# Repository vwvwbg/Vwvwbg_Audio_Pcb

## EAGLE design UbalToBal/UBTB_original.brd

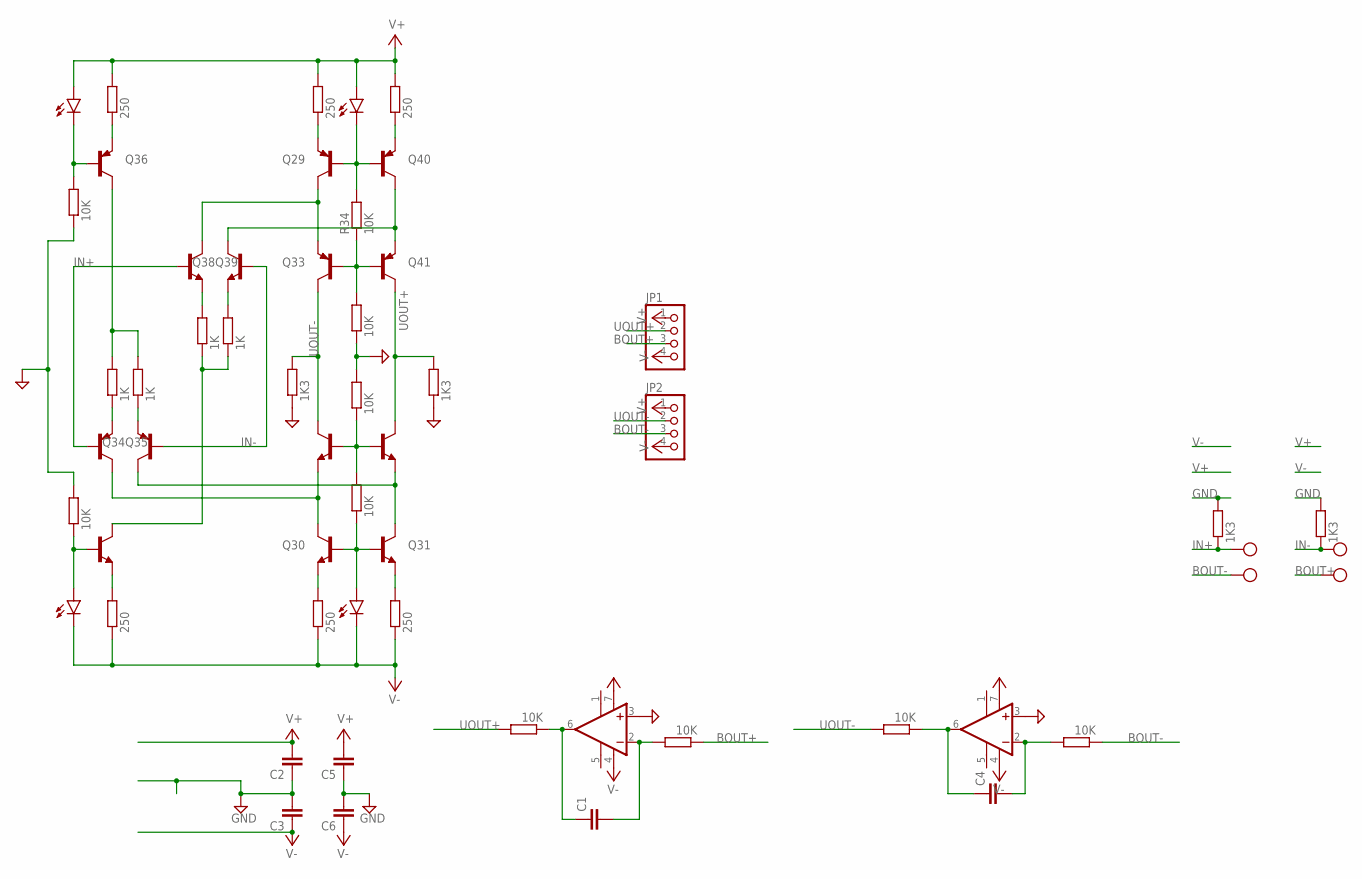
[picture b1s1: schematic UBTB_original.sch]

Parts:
C1, C4: C-EUC1206; C1206
C2, C3, C5, C6: C-EUC0805; C0805
IC1, IC2: OPA627U; SO08
JP1, JP2: PINHD-1X4; 1X04
LED1, LED2, LED3, LED4: LEDCHIPLED_1206; CHIPLED_1206
Q26, Q30, Q31, Q32, Q37, Q38, Q39: BC847CSMD; SOT23
Q29, Q33, Q34, Q35, Q36, Q40, Q41: BC857CSMD; SOT23-BEC
R1, R2, R37, R38: 1K3; MINI_MELF-0204W
R16, R17, R29, R32, R33, R34, R45, R46, R48, R51: 10K; MINI_MELF-0204W
R22, R23, R35, R36, R43, R44: 250; MINI_MELF-0204W
R39, R40, R41, R42: 1K; MINI_MELF-0204W
X3, X4: CON-PHOENIX-508_MKDSN1,5/2-5,08

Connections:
BOUT+: JP1.3, R17.1, X4.2
BOUT-: JP2.3, R48.1, X3.2
GND: C2.1, C3.2, C5.1, C6.2, IC1.3 (+IN), IC2.3 (+IN), R1.2, R2.2, R32.2, R33.1, R37.1, R38.1, R45.1, R46.2
IN+: Q35.B, Q39.1 (B), R1.1, X3.1
IN-: Q34.B, Q38.1 (B), R2.1, X4.1
unnamed: C4.1, IC2.6 (OUT), R51.1
unnamed: C4.2, IC2.2 (-IN), R48.2
unnamed: C1.2, IC1.2 (-IN), R17.2
unnamed: C1.1, IC1.6 (OUT), R16.1
unnamed: Q30.2 (E), R22.2
unnamed: Q31.2 (E), R23.2
unnamed: Q31.3 (C), Q32.2 (E), Q34.C
unnamed: Q30.3 (C), Q35.C, Q37.2 (E)
unnamed: LED1.A, Q30.1 (B), Q31.1 (B), R29.1
unnamed: Q32.1 (B), Q37.1 (B), R29.2, R32.1
unnamed: Q33.B, Q41.B, R33.2, R34.1
unnamed: Q29.C, Q33.E, Q39.3 (C)
unnamed: LED2.C, Q29.B, Q40.B, R34.2
unnamed: Q38.3 (C), Q40.C, Q41.E
unnamed: Q29.E, R35.1
unnamed: Q40.E, R36.1
unnamed: LED3.C, Q36.B, R45.2
unnamed: Q36.E, R43.1
unnamed: Q36.C, R41.2, R42.2
unnamed: Q34.E, R42.1
unnamed: Q35.E, R41.1
unnamed: Q39.2 (E), R39.2
unnamed: Q38.2 (E), R40.2
unnamed: Q26.3 (C), R39.1, R40.1
unnamed: Q26.2 (E), R44.2
unnamed: LED4.A, Q26.1 (B), R46.1
UOUT+: JP1.2, Q32.3 (C), Q41.C, R16.2, R38.2
UOUT-: JP2.2, Q33.C, Q37.3 (C), R37.2, R51.2
V+: C2.2, C5.2, IC1.7 (V+), IC2.7 (V+), JP1.1, JP2.1, LED2.A, LED3.A, R35.2, R36.2, R43.2
V-: C3.1, C6.1, IC1.4 (V-), IC2.4 (V-), JP1.4, JP2.4, LED1.C, LED4.C, R22.1, R23.1, R44.1

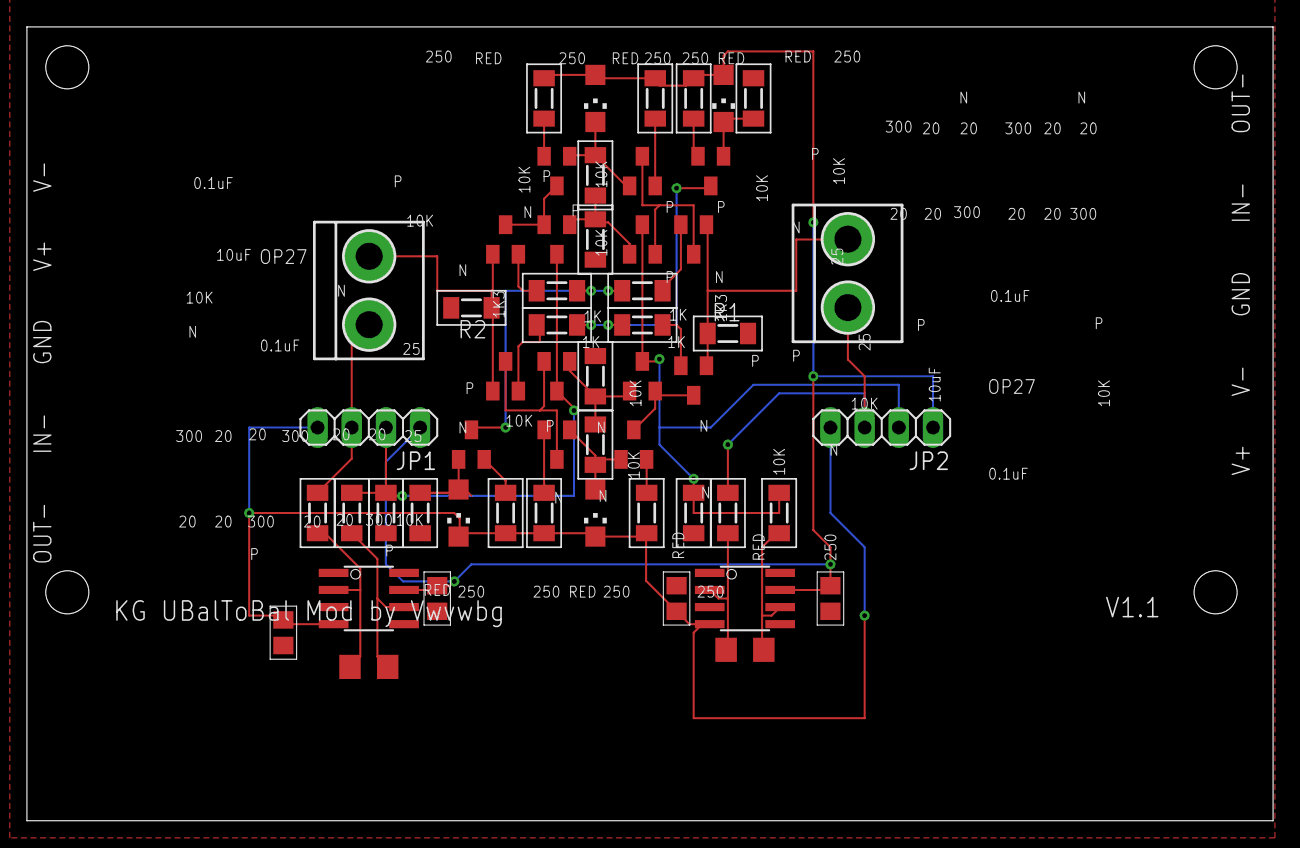
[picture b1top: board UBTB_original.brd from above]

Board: 2 copper layers, 92.6 x 59.0 mm, 54 parts (0 on the bottom side), 35 nets.

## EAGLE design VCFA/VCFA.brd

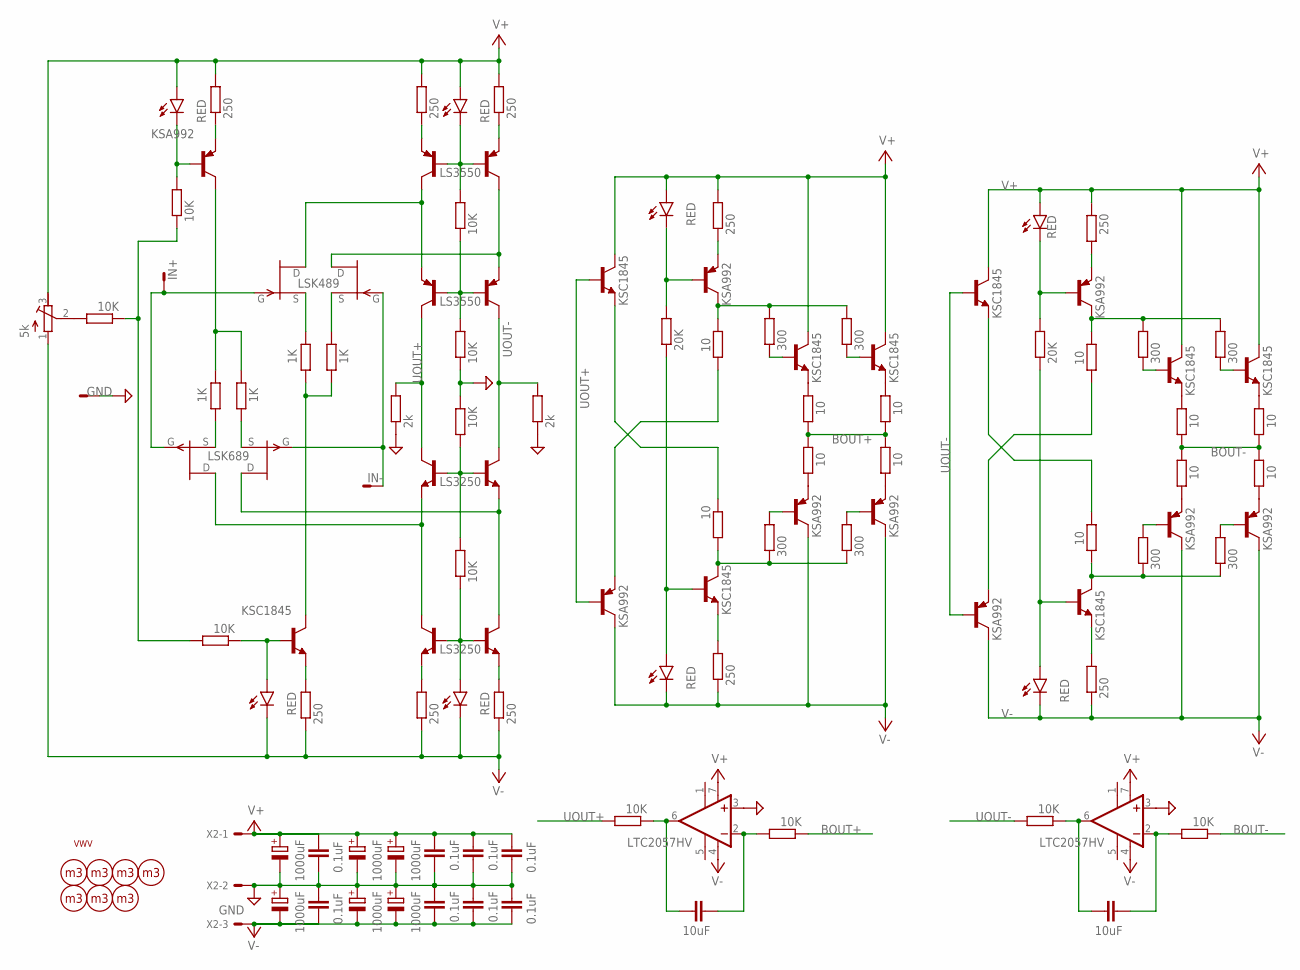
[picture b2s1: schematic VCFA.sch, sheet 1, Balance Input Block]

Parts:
C1, C2, C5, C6, C7, C8: 1000uF; E7,5-16
C3, C4, C14, C15: 0.1uF; C0805
C9, C10, C11, C12: 0.1uF; C050-045X075
C13, C16: 10uF; C1206
H1, H2, H3, H4, H5, H6, H7: HOLE; M3_HOLE
IC1, IC2: LTC2057HV; SO08
LED1, LED2, LED3, LED4, LED5, LED6, LED7, LED8: RED; LED_SML1206
Q1: LSK689; SOT-23-6
Q2, Q10, Q11, Q14, Q16, Q18, Q19, Q22, Q24: KSA992; TRANSISTOR_TO92-ECB_P
Q3, Q9, Q12, Q13, Q15, Q17, Q20, Q21, Q23: KSC1845; TRANSISTOR_TO92-ECB_N
Q4: LSK489; SOT-23-6
Q5, Q8: LS3550; SOT-23-6
Q6, Q7: LS3250; SOT-23-6
R1: 5k; RTRIM3296W
R2, R3, R4, R14, R15, R16, R17, R21, R29, R36, R44: 10K; MINI_MELF-0204W
R5, R7, R12, R13, R18, R19, R23, R26, R38, R41: 250; MINI_MELF-0204W
R6, R8, R9, R10: 1K; MINI_MELF-0204W
R11, R20: 2k; MINI_MELF-0204W
R22, R37: 20K; MINI_MELF-0204W
R24, R25, R30, R31, R34, R35, R39, R40, R45, R46, R49, R50: 10; MINI_MELF-0204W
R27, R28, R32, R33, R42, R43, R47, R48: 300; MINI_MELF-0204W
S1: VWV
X1, X2: KK-156-3

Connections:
BOUT+: R29.1, R30.1, R31.2, R34.1, R35.2; also elsewhere on the board
BOUT-: R44.1, R45.1, R46.2, R49.1, R50.2; also elsewhere on the board
GND: C1.-, C2.+, C3.1, C4.2, C5.-, C6.+, C7.-, C8.+, C9.2, C10.1, C11.2, C12.1, C14.1, C15.2, IC1.3 (+IN), IC2.3 (+IN), R11.1, R15.1, R16.2, R20.1, X1.2, X2.2; also elsewhere on the board
IN+: Q1.1 (G), Q4.1 (G), X1.1
IN-: Q1.4 (G), Q4.4 (G), X1.3
unnamed: Q8.2 (E), R12.1
unnamed: Q10.E, R24.2
unnamed: Q12.E, R26.2
unnamed: Q11.E, R23.1
unnamed: LED5.C, Q11.B, R22.2
unnamed: LED6.A, Q12.B, R22.1
unnamed: Q11.C, R24.1, R27.2, R32.2
unnamed: Q12.C, R25.2, R28.1, R33.1
unnamed: Q9.E, R25.1
unnamed: Q13.B, R27.1
unnamed: Q13.E, R30.2
unnamed: Q16.B, R33.2
unnamed: Q15.B, R32.1
unnamed: Q14.B, R28.2
unnamed: Q14.E, R31.1
unnamed: C13.2, IC1.2 (-IN), R29.2
unnamed: Q15.E, R34.2
unnamed: Q16.E, R35.1
unnamed: C13.1, IC1.6 (OUT), R21.1
unnamed: Q8.5 (E), R18.1
unnamed: R2.1, R3.1, R4.2
unnamed: Q20.E, R41.2
unnamed: Q19.E, R38.1
unnamed: LED7.C, Q19.B, R37.2
unnamed: LED8.A, Q20.B, R37.1
unnamed: Q19.C, R39.1, R42.2, R47.2
unnamed: Q20.C, R40.2, R43.1, R48.1
unnamed: Q18.E, R39.2
unnamed: Q17.E, R40.1
unnamed: Q21.B, R42.1
unnamed: Q22.B, R43.2
unnamed: Q23.B, R47.1
unnamed: Q24.B, R48.2
unnamed: Q21.E, R45.2
unnamed: Q22.E, R46.1
unnamed: Q23.E, R49.2
unnamed: Q24.E, R50.1
unnamed: C16.2, IC2.2 (-IN), R44.2
unnamed: C16.1, IC2.6 (OUT), R36.1
unnamed: R1.2 (S), R2.2
unnamed: Q7.5 (E), R13.2
unnamed: Q7.2 (E), R19.2
unnamed: Q1.5 (D), Q6.2 (E), Q7.4 (C)
unnamed: Q1.2 (D), Q6.5 (E), Q7.6 (C)
unnamed: LED4.A, Q7.1 (B), Q7.3 (B), R17.1
unnamed: Q6.1 (B), Q6.3 (B), R16.1, R17.2
unnamed: LED2.A, Q3.B, R4.1
unnamed: Q5.1 (B), Q5.3 (B), R14.1, R15.2
unnamed: Q4.2 (D), Q5.5 (E), Q8.4 (C)
unnamed: LED3.C, Q8.1 (B), Q8.3 (B), R14.2
unnamed: Q4.5 (D), Q5.2 (E), Q8.6 (C)
unnamed: LED1.C, Q2.B, R3.2
unnamed: Q2.E, R5.1
unnamed: Q2.C, R6.2, R8.2
unnamed: Q1.6 (S), R8.1
unnamed: Q1.3 (S), R6.1
unnamed: Q4.3 (S), R9.2
unnamed: Q4.6 (S), R10.2
unnamed: Q3.C, R9.1, R10.1
unnamed: Q3.E, R7.2
UOUT+: Q5.6 (C), Q6.6 (C), Q9.B, Q10.B, R11.2, R21.2
UOUT-: Q5.4 (C), Q6.4 (C), Q17.B, Q18.B, R20.2, R36.2
V+: C1.+, C3.2, C5.+, C7.+, C9.1, C11.1, C14.2, IC1.7 (V+), IC2.7 (V+), LED1.A, LED3.A, LED5.A, LED7.A, Q9.C, Q13.C, Q15.C, Q17.C, Q21.C, Q23.C, R1.3 (E), R5.2, R12.2, R18.2, R23.2, R38.2, X2.1; also elsewhere on the board
V-: C2.-, C4.1, C6.-, C8.-, C10.2, C12.2, C15.1, IC1.4 (V-), IC2.4 (V-), LED2.C, LED4.C, LED6.C, LED8.C, Q10.C, Q14.C, Q16.C, Q18.C, Q22.C, Q24.C, R1.1 (A), R7.1, R13.1, R19.1, R26.1, R41.1, X2.3; also elsewhere on the board

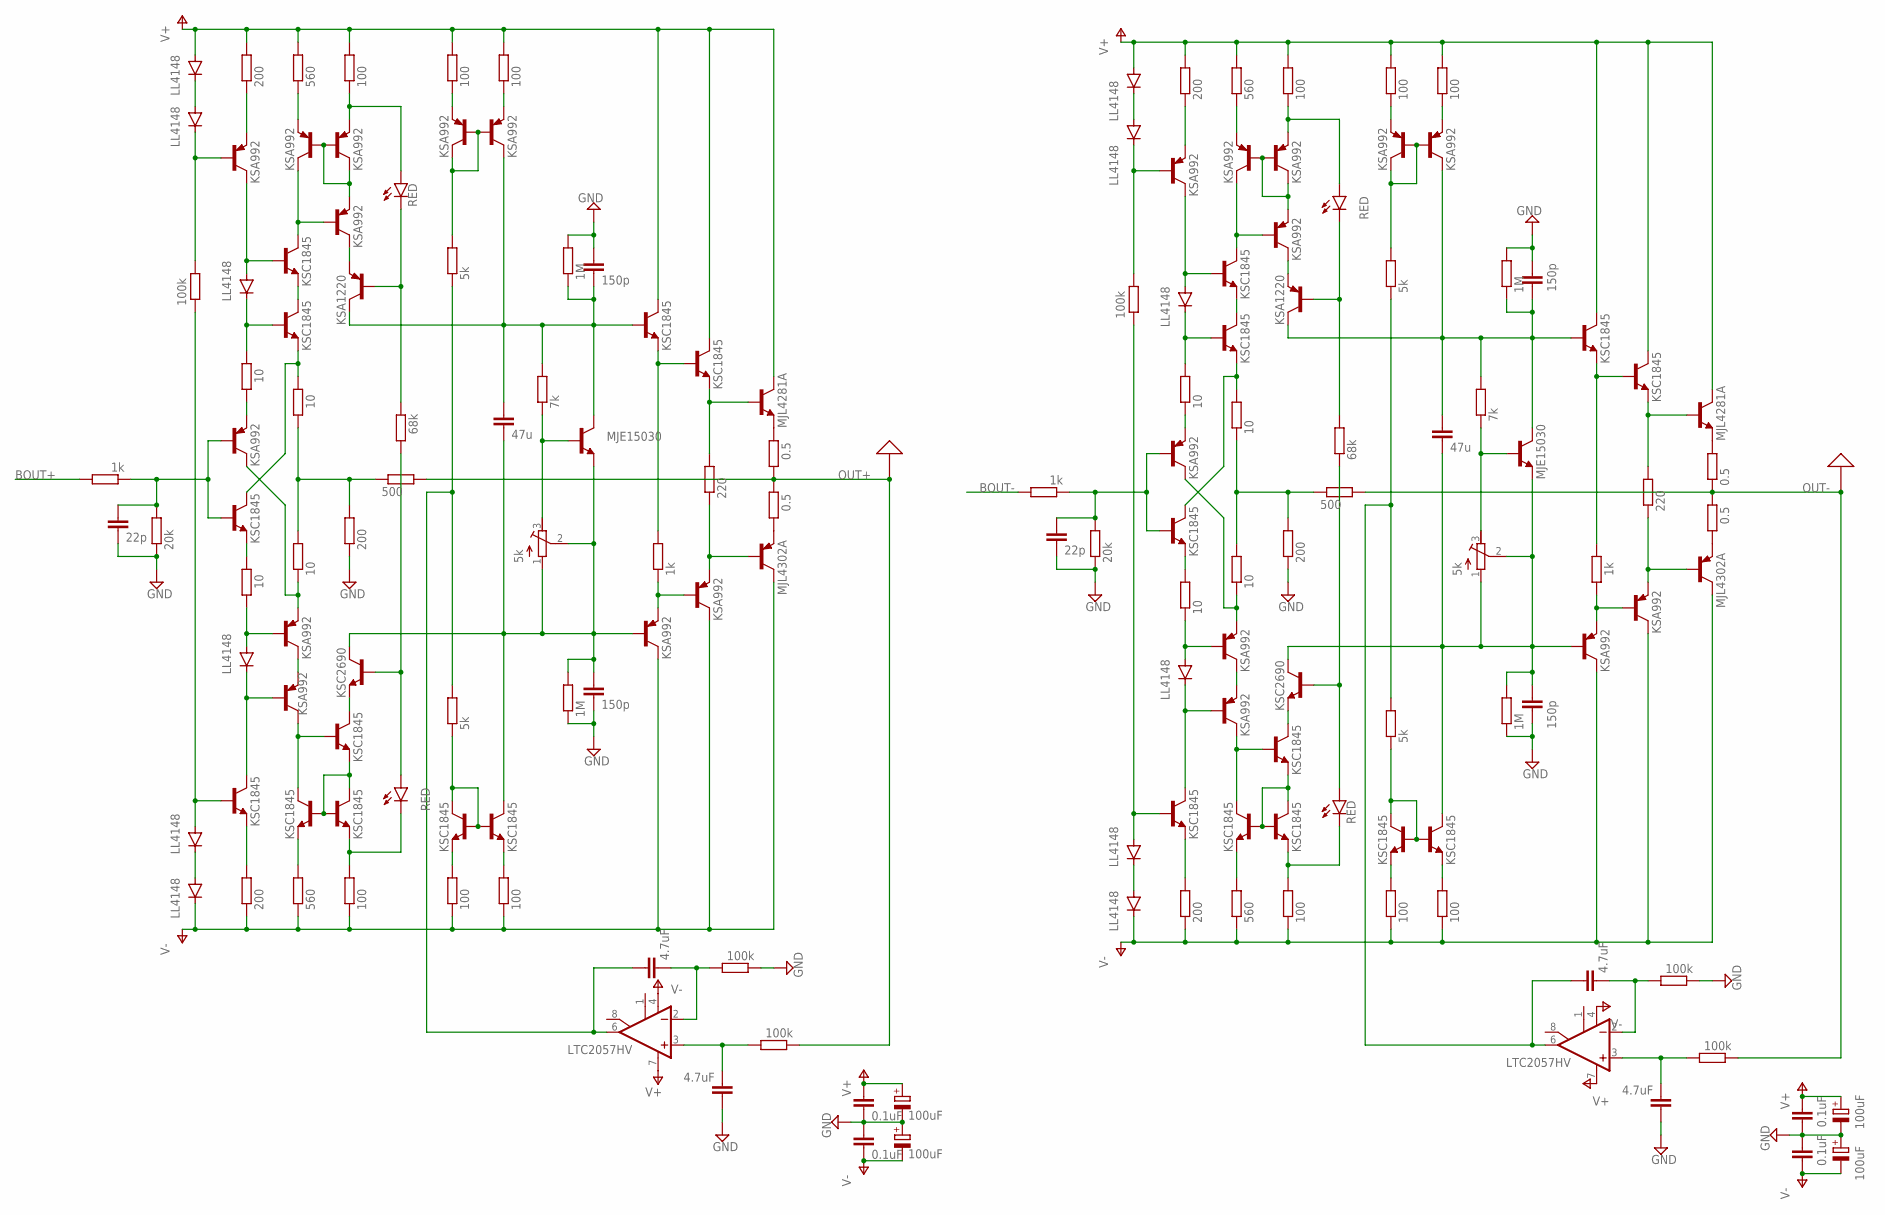
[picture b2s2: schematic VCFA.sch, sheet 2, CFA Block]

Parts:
C17, C27: 22p; C0805
C18, C28: 47u; C1210
C19, C20, C29, C30: 150p; C0805
C21, C22, C31, C32: 4.7uF; C1210
C23, C24, C33, C34: 0.1uF; C0603K
C25, C26, C35, C36: 100uF; E3,5-8
D1, D2, D3, D4, D5, D6, D7, D8, D9, D10, D11, D12: LL4148; SOD80C
IC3, IC4: LTC2057HV; SOIC8
LED9, LED10, LED11, LED12: RED; LED_SML1206
PAD1, PAD2: PAD; PAD-16
Q25, Q26, Q31, Q32, Q33, Q35, Q36, Q41, Q43, Q47, Q49, Q52, Q53, Q58, Q59, Q60, Q62, Q63, Q68, Q70, Q74, Q76: KSA992; TRANSISTOR_TO92-ECB_P
Q27, Q28, Q29, Q30, Q34, Q37, Q38, Q42, Q44, Q46, Q48, Q54, Q55, Q56, Q57, Q61, Q64, Q65, Q69, Q71, Q73, Q75: KSC1845; TRANSISTOR_TO92-ECB_N
Q39, Q66: KSA1220; TRANSISTOR_TO126_P
Q40, Q67: KSC2690; TRANSISTOR_TO126_N
Q45, Q72: MJE15030; TRANSISTOR_TO220_BCE_N
Q50, Q77: MJL4281A; TRANSISTOR_TO247_BCE_N
Q51, Q78: MJL4302A; TRANSISTOR_TO247_BCE_P
R51, R77, R83, R109: 1k; MINI_MELF-0204W
R52, R84: 20k; MINI_MELF-0204W
R53, R79, R82, R85, R111, R114: 100k; MINI_MELF-0204W
R54, R57, R63, R86, R89, R95: 200; MINI_MELF-0204W
R55, R56, R59, R60, R87, R88, R91, R92: 10; MINI_MELF-0204W
R58, R61, R90, R93: 560; MINI_MELF-0204W
R62, R64, R67, R70, R71, R72, R94, R96, R99, R102, R103, R104: 100; MINI_MELF-0204W
R65, R97: 68k; MINI_MELF-0204W
R66, R98: 500; MINI_MELF-0204W
R68, R69, R100, R101: 5k; MINI_MELF-0204W
R73, R105: 7k; MINI_MELF-0204W
R74, R106: 5k; RTRIM3296W
R75, R76, R107, R108: 1M; MINI_MELF-0204W
R78, R110: 220; MINI_MELF-0204W
R80, R81, R112, R113: 0.5; R2512

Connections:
BOUT+: R51.2; also elsewhere on the board
BOUT-: R83.2; also elsewhere on the board
GND: C17.2, C19.1, C20.2, C22.1, C23.2, C24.1, C25.-, C26.+, C27.2, C29.1, C30.2, C32.1, C33.2, C34.1, C35.-, C36.+, R52.1, R63.1, R75.2, R76.1, R79.1, R84.1, R95.1, R107.2, R108.1, R111.1; also elsewhere on the board
unnamed: Q25.E, R54.1
unnamed: D5.A, Q25.C, Q29.B
unnamed: D1.C, D2.A
unnamed: D2.C, Q25.B, R53.2
unnamed: D5.C, Q30.B, R55.2
unnamed: Q29.E, Q30.C
unnamed: Q27.C, Q30.E, R59.2
unnamed: R59.1, R60.2, R63.2, R66.1
unnamed: Q26.C, Q31.E, R60.1
unnamed: D6.A, Q31.B, R56.1
unnamed: D6.C, Q28.C, Q32.B
unnamed: Q28.E, R57.2
unnamed: D3.C, D4.A
unnamed: Q31.C, Q32.E
unnamed: Q26.E, R55.1
unnamed: Q27.E, R56.2
unnamed: C17.1, Q26.B, Q27.B, R51.1, R52.2
unnamed: Q29.C, Q33.C, Q36.B
unnamed: Q33.B, Q35.B, Q35.C, Q36.E
unnamed: Q33.E, R58.1
unnamed: LED9.A, Q35.E, R62.1
unnamed: Q36.C, Q39.E
unnamed: LED9.C, Q39.B, R65.2
unnamed: Q34.B, Q37.E, Q38.B, Q38.C
unnamed: LED10.C, Q38.E, R64.2
unnamed: Q34.E, R61.2
unnamed: Q32.C, Q34.C, Q37.B
unnamed: Q37.C, Q40.E
unnamed: LED10.A, Q40.B, R65.1
unnamed: C18.1, C19.2, Q39.C, Q43.C, Q45.C, Q46.B, R73.2, R75.1
unnamed: Q41.B, Q41.C, Q43.B, R68.2
unnamed: Q42.B, Q42.C, Q44.B, R69.1
unnamed: Q41.E, R67.1
unnamed: Q43.E, R71.1
unnamed: Q42.E, R70.2
unnamed: Q44.E, R72.2
unnamed: Q46.E, Q48.B, R77.2
unnamed: Q47.E, Q49.B, R77.1
unnamed: C18.2, C20.1, Q40.C, Q44.C, Q45.E, Q47.B, R74.1 (A), R74.2 (S), R76.2
unnamed: Q48.E, Q50.B, R78.2
unnamed: Q49.E, Q51.B, R78.1
unnamed: Q50.E, R80.2
unnamed: Q51.E, R81.1
unnamed: C21.2, IC3.2 (-IN), R79.2
unnamed: C22.2, IC3.3 (+IN), R82.2
unnamed: D3.A, Q28.B, R53.1
unnamed: Q45.B, R73.1, R74.3 (E)
unnamed: C21.1, IC3.6 (OUT), R68.1, R69.2
unnamed: Q52.E, R86.1
unnamed: D11.A, Q52.C, Q56.B
unnamed: D7.C, D8.A
unnamed: D8.C, Q52.B, R85.2
unnamed: D11.C, Q57.B, R87.2
unnamed: Q56.E, Q57.C
unnamed: Q54.C, Q57.E, R91.2
unnamed: R91.1, R92.2, R95.2, R98.1
unnamed: Q53.C, Q58.E, R92.1
unnamed: D12.A, Q58.B, R88.1
unnamed: D12.C, Q55.C, Q59.B
unnamed: Q55.E, R89.2
unnamed: D9.C, D10.A
unnamed: Q58.C, Q59.E
unnamed: Q53.E, R87.1
unnamed: Q54.E, R88.2
unnamed: C27.1, Q53.B, Q54.B, R83.1, R84.2
unnamed: Q56.C, Q60.C, Q63.B
unnamed: Q60.B, Q62.B, Q62.C, Q63.E
unnamed: Q60.E, R90.1
unnamed: LED11.A, Q62.E, R94.1
unnamed: Q63.C, Q66.E
unnamed: LED11.C, Q66.B, R97.2
unnamed: Q61.B, Q64.E, Q65.B, Q65.C
unnamed: LED12.C, Q65.E, R96.2
unnamed: Q61.E, R93.2
unnamed: Q59.C, Q61.C, Q64.B
unnamed: Q64.C, Q67.E
unnamed: LED12.A, Q67.B, R97.1
unnamed: C28.1, C29.2, Q66.C, Q70.C, Q72.C, Q73.B, R105.2, R107.1
unnamed: Q68.B, Q68.C, Q70.B, R100.2
unnamed: Q69.B, Q69.C, Q71.B, R101.1
unnamed: Q68.E, R99.1
unnamed: Q70.E, R103.1
unnamed: Q69.E, R102.2
unnamed: Q71.E, R104.2
unnamed: Q73.E, Q75.B, R109.2
unnamed: Q74.E, Q76.B, R109.1
unnamed: C28.2, C30.1, Q67.C, Q71.C, Q72.E, Q74.B, R106.1 (A), R106.2 (S), R108.2
unnamed: Q75.E, Q77.B, R110.2
unnamed: Q76.E, Q78.B, R110.1
unnamed: Q77.E, R112.2
unnamed: Q78.E, R113.1
unnamed: C31.2, IC4.2 (-IN), R111.2
unnamed: C32.2, IC4.3 (+IN), R114.2
unnamed: D9.A, Q55.B, R85.1
unnamed: Q72.B, R105.1, R106.3 (E)
unnamed: C31.1, IC4.6 (OUT), R100.1, R101.2
OUT+: PAD1.P$1, R66.2, R80.1, R81.2, R82.1
OUT-: PAD2.P$1, R98.2, R112.1, R113.2, R114.1
V+: C23.1, C25.+, C33.1, C35.+, D1.A, D7.A, IC3.7 (V+), IC4.7 (V+), Q46.C, Q48.C, Q50.C, Q73.C, Q75.C, Q77.C, R54.2, R58.2, R62.2, R67.2, R71.2, R86.2, R90.2, R94.2, R99.2, R103.2; also elsewhere on the board
V-: C24.2, C26.-, C34.2, C36.-, D4.C, D10.C, IC3.4 (V-), IC4.4 (V-), Q47.C, Q49.C, Q51.C, Q74.C, Q76.C, Q78.C, R57.1, R61.1, R64.1, R70.1, R72.1, R89.1, R93.1, R96.1, R102.1, R104.1; also elsewhere on the board

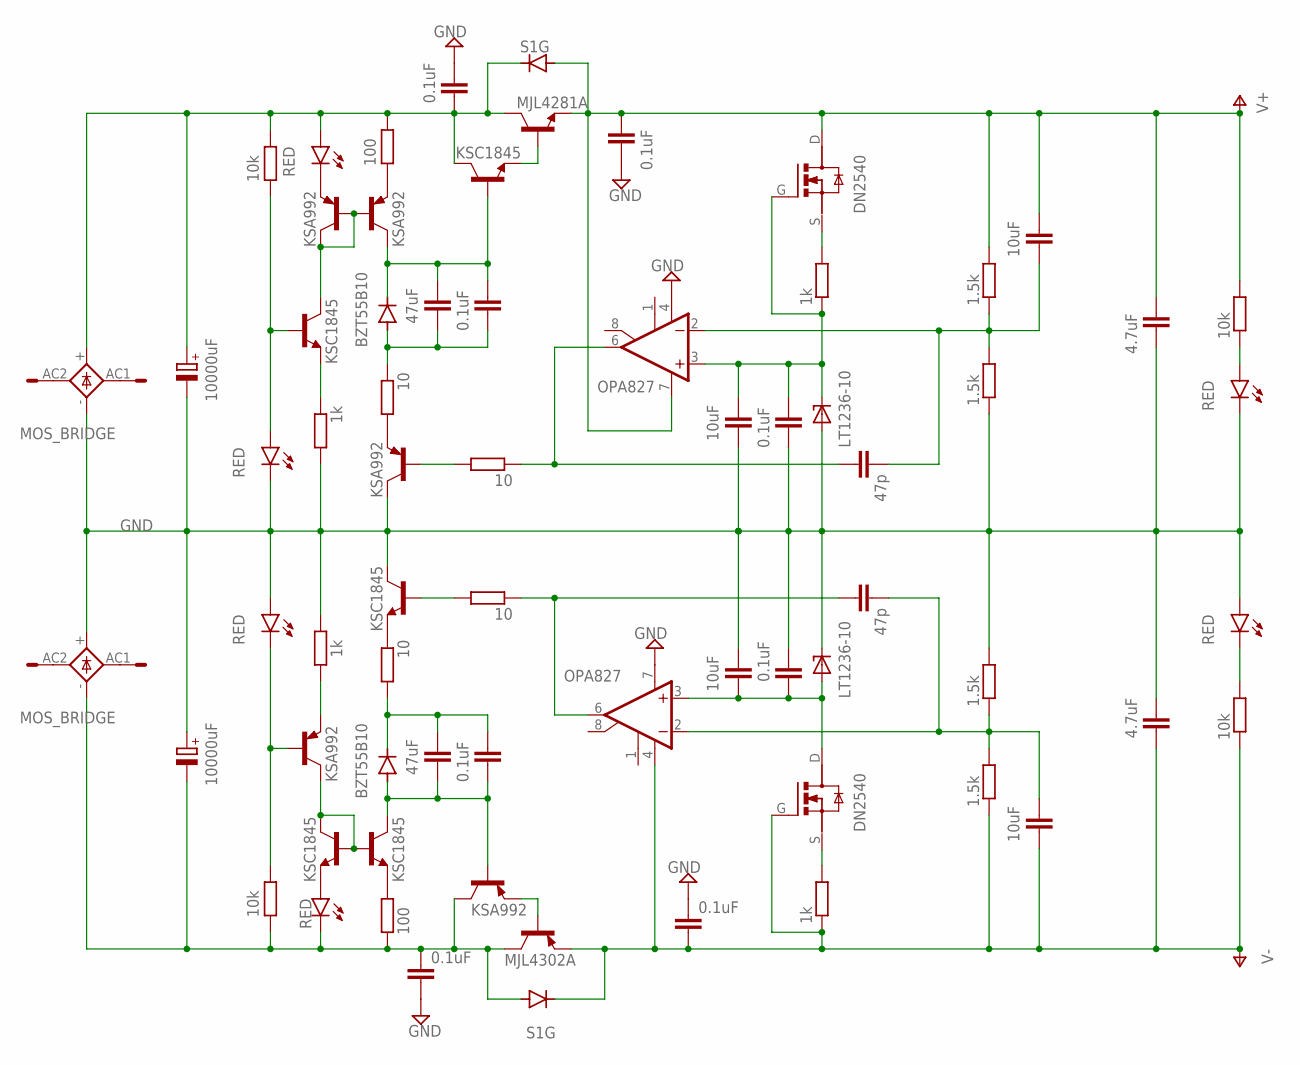
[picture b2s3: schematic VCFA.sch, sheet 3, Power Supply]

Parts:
B1, B2: MOS_BRIDGE; GBU4S
C37, C38: 10000uF; EB35D
C39, C42: 0.1uF; C050-075X075
C40, C41: 47uF; C1206
C43, C44, C45, C46, C49, C50: 0.1uF; C0805
C47, C48, C53, C54: 10uF; C1206
C51, C52: 47p; C0805
C55, C56: 4.7uF; C050-075X075
D13, D14: BZT55B10; SOD80C
D15, D16: S1G; DO214AA
D17, D18: LT1236-10; SO8
IC5, IC6: OPA827; SOIC8
LED13, LED14, LED15, LED16, LED17, LED18: RED; LED_SML1206
Q79, Q82, Q84, Q86, Q87: KSC1845; TRANSISTOR_TO92-ECB_N
Q80, Q81, Q83, Q85, Q88: KSA992; TRANSISTOR_TO92-ECB_P
Q89: MJL4281A; TRANSISTOR_TO247_BCE_N
Q90: MJL4302A; TRANSISTOR_TO247_BCE_P
Q91, Q92: DN2540; TRANSISTOR_TO92-SGD_N
R115, R116, R131, R132: 10k; MINI_MELF-0204W
R117, R118, R125, R126: 1k; MINI_MELF-0204W
R119, R122: 100; MINI_MELF-0204W
R120, R121, R123, R124: 10; MINI_MELF-0204W
R127, R128, R129, R130: 1.5k; MINI_MELF-0204W
X3, X4: KK-156-2

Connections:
GND: B1.-, B2.+, C37.-, C38.+, C39.1, C42.2, C45.1, C46.2, C47.2, C48.1, C49.2, C50.1, C55.1, C56.2, D17.4 (GND), D18.6 (OUT), IC5.7 (V+), IC6.4 (V-), LED13.C, LED14.A, LED17.C, LED18.A, Q85.C, Q86.C, R117.2, R118.1, R128.1, R129.2; also elsewhere on the board
unnamed: Q79.C, Q81.B, Q81.C, Q83.B
unnamed: LED15.C, Q81.E
unnamed: Q83.E, R119.2
unnamed: B1.+, C37.+, C42.1, D15.C, LED15.A, Q87.C, Q89.C, R115.1, R119.1
unnamed: C40.1, C43.1, D13.C, Q83.C, Q87.B
unnamed: C40.2, C43.2, D13.A, R120.1
unnamed: Q85.E, R120.2
unnamed: Q79.E, R117.1
unnamed: LED13.A, Q79.B, R115.2
unnamed: Q80.E, R118.2
unnamed: LED14.C, Q80.B, R116.1
unnamed: Q86.E, R121.1
unnamed: C41.1, C44.1, D14.C, R121.2
unnamed: C41.2, C44.2, D14.A, Q84.C, Q88.B
unnamed: Q80.C, Q82.B, Q82.C, Q84.B
unnamed: Q84.E, R122.1
unnamed: LED16.A, Q82.E
unnamed: Q88.E, Q90.B
unnamed: Q87.E, Q89.B
unnamed: C51.1, IC6.6 (OUT), R123.1
unnamed: C52.1, IC5.6 (OUT), R124.1
unnamed: Q86.B, R124.2
unnamed: Q85.B, R123.2
unnamed: C51.2, C53.2, IC6.2 (-IN), R127.1, R128.2
unnamed: C47.1, C49.1, D17.6 (OUT), IC6.3 (+IN), Q91.G, R125.1
unnamed: Q91.S, R125.2
unnamed: C48.2, C50.2, D18.4 (GND), IC5.3 (+IN), Q92.D
unnamed: Q92.S, R126.2
unnamed: C52.2, C54.1, IC5.2 (-IN), R129.1, R130.2
unnamed: LED18.C, R132.2
unnamed: LED17.A, R131.1
unnamed: B2.-, C38.-, C39.2, D16.A, LED16.C, Q88.C, Q90.C, R116.2, R122.2
unnamed: B1.AC2 (AC1), X3.1
unnamed: B1.AC1 (AC2), X3.2
unnamed: B2.AC2 (AC1), X4.2
unnamed: B2.AC1 (AC2), X4.1
V+: C45.2, C53.1, C55.2, D15.A, IC6.7 (V+), Q89.E, Q91.D, R127.2, R131.2; also elsewhere on the board
V-: C46.1, C54.2, C56.1, D16.C, IC5.4 (V-), Q90.E, Q92.G, R126.1, R130.1, R132.1; also elsewhere on the board

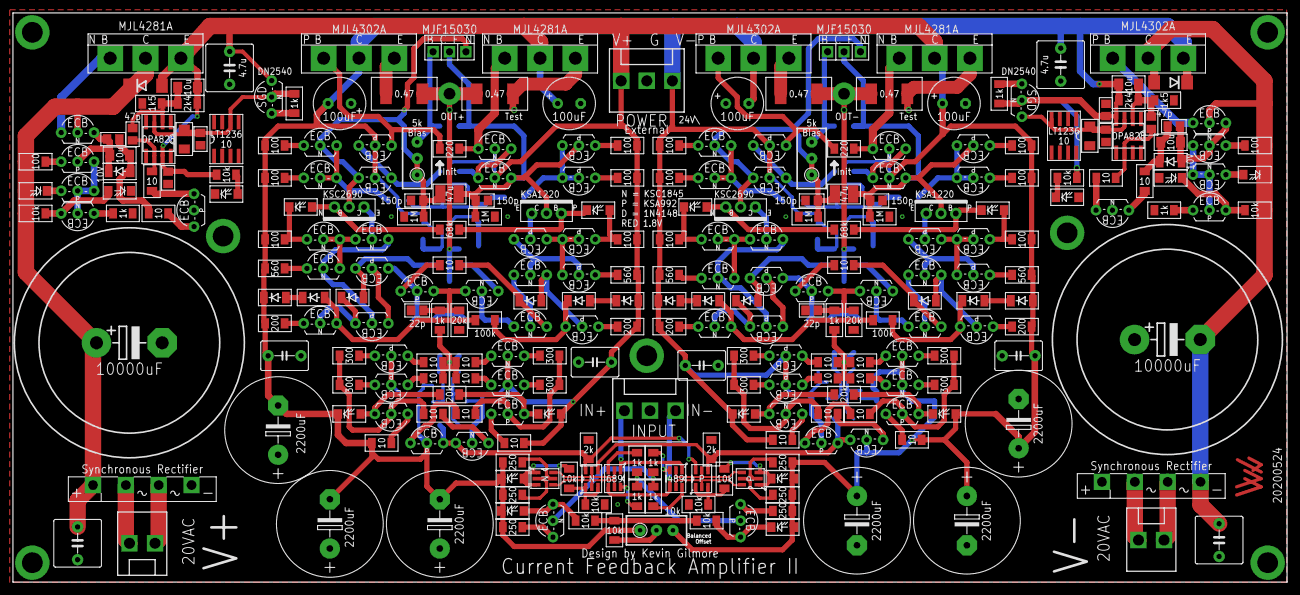
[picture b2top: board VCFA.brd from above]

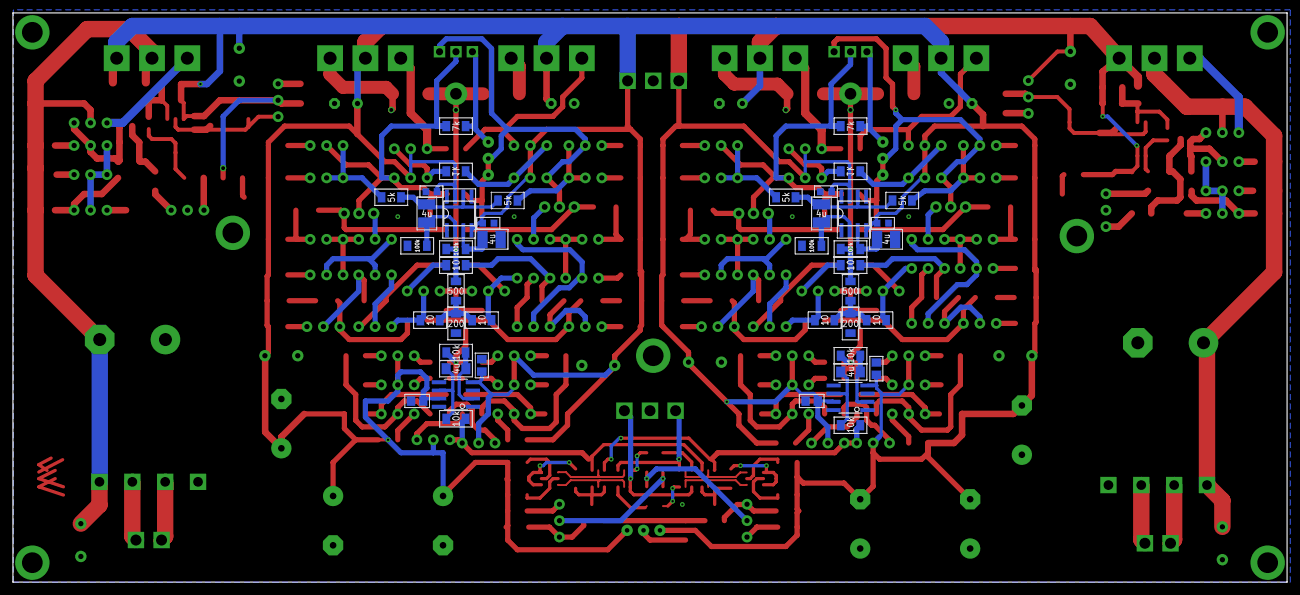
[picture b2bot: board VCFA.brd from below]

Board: 2 copper layers, 197.0 x 88.0 mm, 338 parts (45 on the bottom side), 203 nets.

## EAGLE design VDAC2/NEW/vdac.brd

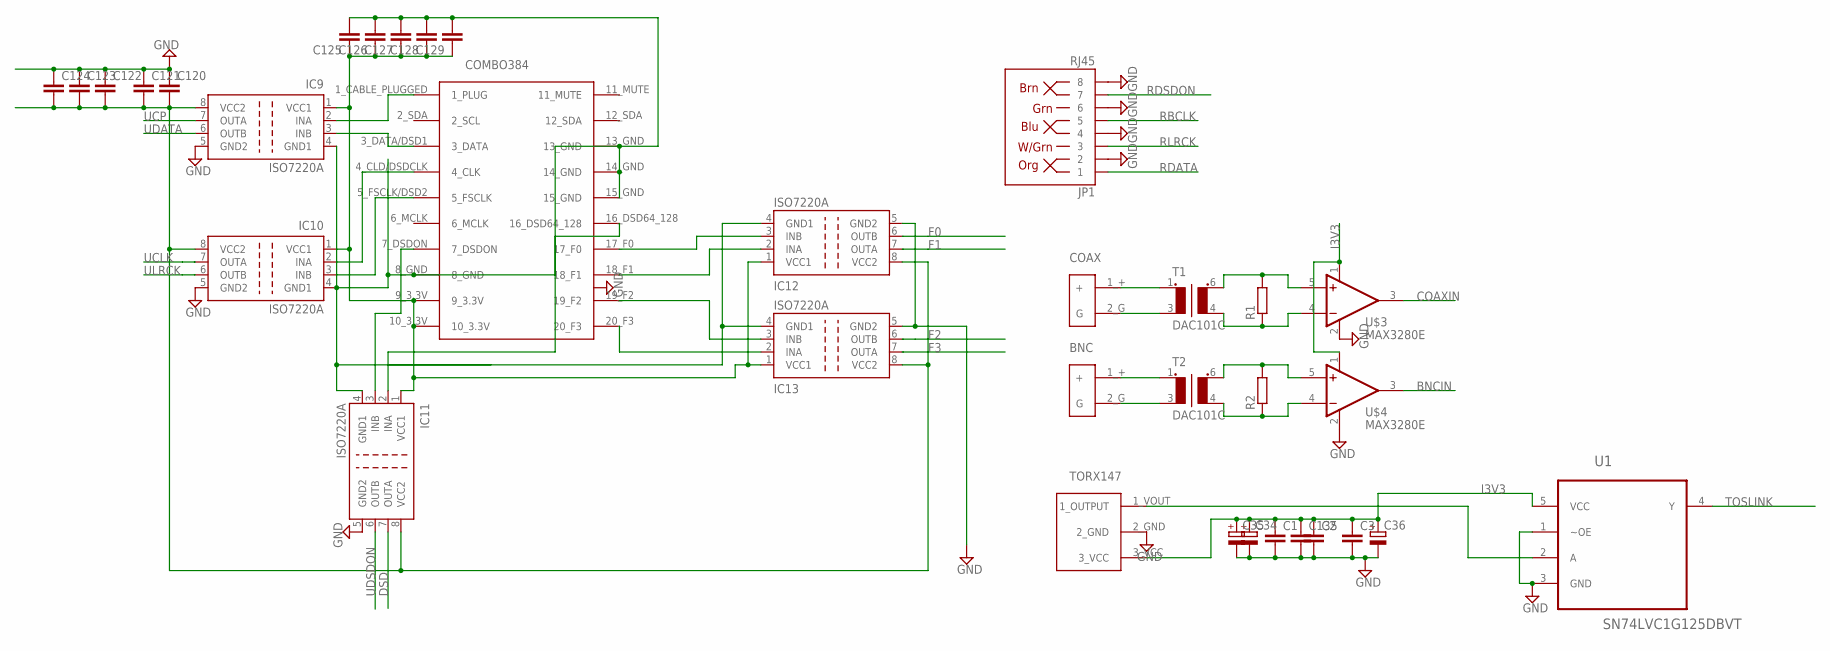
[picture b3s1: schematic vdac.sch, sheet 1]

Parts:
BNC: RCA
C1, C2, C3, C120, C121, C122, C123, C124, C125, C126, C127, C128, C129, C135: C-EUC0805; C0805
C34, C35, C36: CPOL-EUSP-CAP-CX; SP-CAP-CX
COAX: RCA
IC9, IC10, IC11, IC12, IC13: ISO7220A; SO-08
JP1: RJ45; RJ45-8
R1, R2: R-EU_MELF0204W; MINI_MELF-0204W
T1, T2: DAC101C; DAC101
U1: SN74LVC1G125DBVT; SOT95P280X145-5N
U$1: COMBO384
U$2: TORX147
U$3, U$4: MAX3280E; SOT23-5L

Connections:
BNCIN: U$4.3 (OUT); also elsewhere on the board
COAXIN: U$3.3 (OUT); also elsewhere on the board
DSD: IC11.7 (OUTA); also elsewhere on the board
F0: IC12.6 (OUTB); also elsewhere on the board
F1: IC12.7 (OUTA); also elsewhere on the board
F2: IC13.6 (OUTB); also elsewhere on the board
F3: IC13.7 (OUTA); also elsewhere on the board
GND: C1.2, C2.2, C3.2, C34.-, C35.-, C36.-, C120.1, C121.1, C122.1, C123.1, C124.1, C135.2, IC9.5 (GND2), IC10.5 (GND2), IC11.5 (GND2), IC12.5 (GND2), IC13.5 (GND2), JP1.2, JP1.4, JP1.6, JP1.8, U1.1 (~OE), U1.3 (GND), U$2.2_GND, U$3.2 (V-), U$4.2 (V-); also elsewhere on the board
I3V3: C1.1, C2.1, C3.1, C34.+, C35.+, C36.+, C120.2, C121.2, C122.2, C123.2, C124.2, C135.1, IC9.8 (VCC2), IC10.8 (VCC2), IC11.8 (VCC2), IC12.8 (VCC2), IC13.8 (VCC2), U1.5 (VCC), U$2.3_VCC, U$3.1 (V+), U$4.1 (V+); also elsewhere on the board
unnamed: COAX.1_+ (+), T1.1
unnamed: COAX.2_G (G), T1.3 (P2)
unnamed: BNC.1_+ (+), T2.1
unnamed: BNC.2_G (G), T2.3 (P2)
unnamed: R1.2, T1.6 (S1), U$3.5 (+IN)
unnamed: R1.1, T1.4 (S2), U$3.4 (-IN)
unnamed: R2.2, T2.6 (S1), U$4.5 (+IN)
unnamed: R2.1, T2.4 (S2), U$4.4 (-IN)
unnamed: U1.2 (A), U$2.1_VOUT (1_OUTPUT)
unnamed: IC9.2 (INA), U$1.1_CABLE_PLUGGED (1_PLUG)
unnamed: IC9.3 (INB), U$1.3_DATA/DSD1 (3_DATA)
unnamed: IC10.2 (INA), U$1.4_CLD/DSDCLK (4_CLK)
unnamed: IC10.3 (INB), U$1.5_FSCLK/DSD2 (5_FSCLK)
unnamed: IC11.3 (INB), U$1.7_DSDON
unnamed: C125.1, C126.1, C127.1, C128.1, C129.1, IC9.1 (VCC1), IC10.1 (VCC1), IC11.1 (VCC1), IC12.1 (VCC1), IC13.1 (VCC1), U$1.9_3.3V, U$1.10_3.3V
unnamed: IC11.2 (INA), U$1.16_DSD64_128
unnamed: IC12.3 (INB), U$1.17_F0
unnamed: IC12.2 (INA), U$1.18_F1
unnamed: IC13.3 (INB), U$1.19_F2
unnamed: IC13.2 (INA), U$1.20_F3
RBCLK: JP1.5; also elsewhere on the board
RDATA: JP1.1; also elsewhere on the board
RDSDON: JP1.7; also elsewhere on the board
RLRCK: JP1.3; also elsewhere on the board
TOSLINK: U1.4 (Y); also elsewhere on the board
UCLK: IC10.7 (OUTA); also elsewhere on the board
UCP: IC9.7 (OUTA)
UDATA: IC9.6 (OUTB); also elsewhere on the board
UDSDON: IC11.6 (OUTB); also elsewhere on the board
UGND: C125.2, C126.2, C127.2, C128.2, C129.2, IC9.4 (GND1), IC10.4 (GND1), IC11.4 (GND1), IC12.4 (GND1), IC13.4 (GND1), U$1.8_GND, U$1.13_GND, U$1.14_GND, U$1.15_GND
ULRCK: IC10.6 (OUTB); also elsewhere on the board

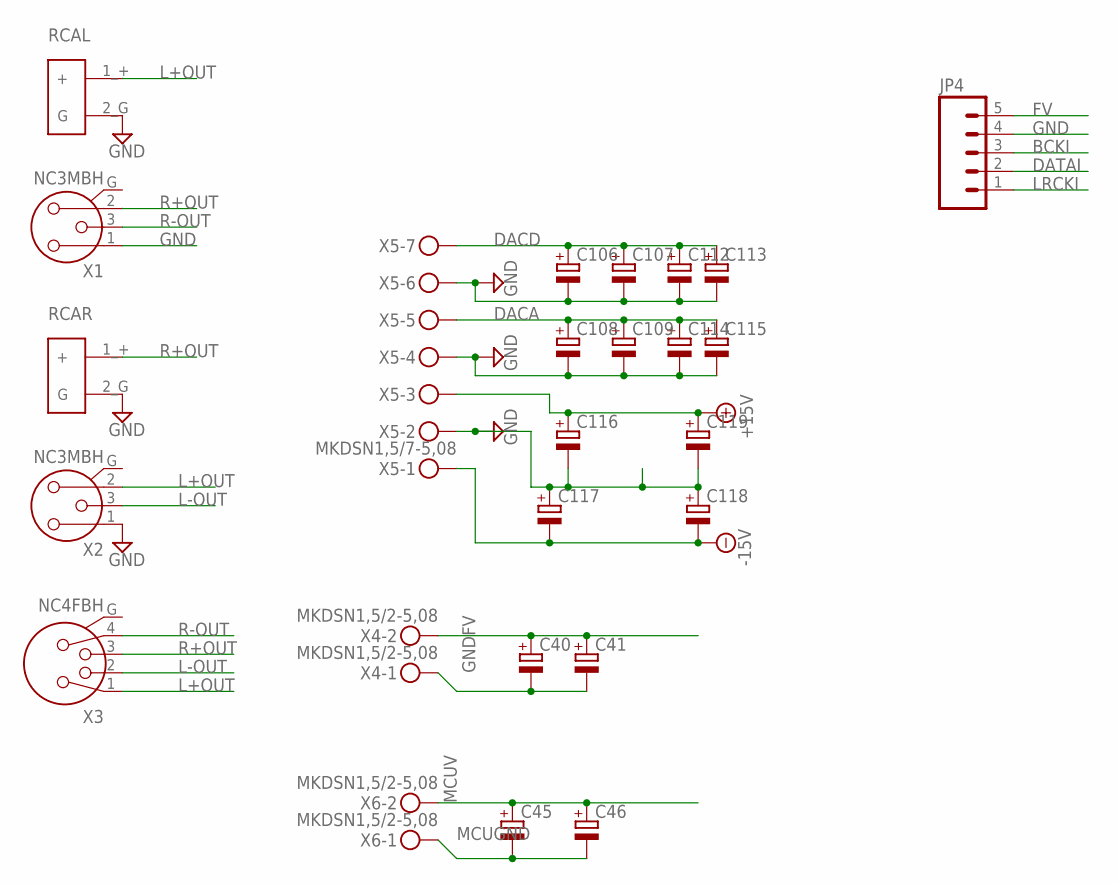
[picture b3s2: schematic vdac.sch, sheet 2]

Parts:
C40, C41, C45, C46, C106, C107, C108, C109, C112, C113, C114, C115, C116, C117, C118, C119: CPOL-EUSP-CAP-CX; SP-CAP-CX
JP4: M05PTH_LONGPADS; 1X05_LONGPADS
RCAL: RCA
RCAR: RCA
X1, X2: NC3MBH
X3: NC4FBH
X4, X6: MKDSN1,5/2-5,08
X5: MKDSN1,5/7-5,08

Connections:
+15V: C116.+, C119.+, X5.3; also elsewhere on the board
-15V: C117.-, C118.-, X5.1; also elsewhere on the board
BCKI: JP4.3; also elsewhere on the board
DACA: C108.+, C109.+, C114.+, C115.+, X5.5
DACD: C106.+, C107.+, C112.+, C113.+, X5.7
DATAI: JP4.2; also elsewhere on the board
FV: C40.+, C41.+, JP4.5, X4.2; also elsewhere on the board
GND: C40.-, C41.-, C106.-, C107.-, C108.-, C109.-, C112.-, C113.-, C114.-, C115.-, C116.-, C117.+, C118.+, C119.-, JP4.4, RCAL.2_G (G), RCAR.2_G (G), X1.1, X2.1, X4.1, X5.2, X5.4, X5.6; also elsewhere on the board
L+OUT: RCAL.1_+ (+), X2.2, X3.1
L-OUT: X2.3, X3.2
LRCKI: JP4.1; also elsewhere on the board
MCUGND: C45.-, C46.-, X6.1; also elsewhere on the board
MCUV: C45.+, C46.+, X6.2; also elsewhere on the board
R+OUT: RCAR.1_+ (+), X1.2, X3.3
R-OUT: X1.3, X3.4

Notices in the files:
parts and their libraries:
SparkFun-Connectors: Licensing: Creative Commons ShareAlike 4.0 International - https://creativecommons.org/licenses/by-sa/4.0
